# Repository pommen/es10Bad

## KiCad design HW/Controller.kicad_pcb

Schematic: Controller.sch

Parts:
1U1: 0,1U; C_0805_HandSoldering
C1: 0,1u; C_0805_HandSoldering
C2: 10u; C_0805_HandSoldering
C3: 10uF; CP_Tantalum_Case-B_EIA-3528-21_Hand
C4, C9: 0.1u; C_0805_HandSoldering
C5: 0,1U; C_0805_HandSoldering
C6, C7: 22pf; C_0805_HandSoldering
C8: 0.1; C_0805_HandSoldering
D1: WS2812B
F1: Polyfuse; LittleFuse_110F_24V
FTDI1: FTDI; Pin_Header_Angled_1x06_Pitch2.54mm
J1: Spare; Pin_Header_Straight_1x04_Pitch2.54mm
J2: +12V_con; TerminalBlock_bornier-2_P5.08mm
J3: LimitUpper; Pin_Header_Straight_1x03_Pitch2.54mm
J4: ControlSwitch; Pin_Header_Straight_1x03_Pitch2.54mm
J5: LimitLower; Pin_Header_Straight_1x03_Pitch2.54mm
J6: Motor_controller_connections; Pin_Header_Straight_1x09_Pitch2.54mm
JP1: Jumper; Pin_Header_Straight_1x03_Pitch2.54mm
R1: 10K; R_0805_HandSoldering
U1: L7805; TO-220-3_Horizontal
U2: ATMEGA328P-AU-Arduino; TQFP-32_7x7mm_Pitch0.8mm
Y1: 8MHZ; Crystal_SMD_HC49-SD_HandSoldering

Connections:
+12V: C2.1, F1.1, J3.1, J4.1, J5.1, U1.1
Dir: J6.2, U2.14
Ena: J6.6, U2.12
Fault: J6.7, U2.15
GND: 1U1.2, C2.2, C3.2, C4.2, C5.2, C6.1, C7.1, C8.2, C9.2, D1.1, FTDI1.5, FTDI1.6, J2.1, J3.2, J4.2, J5.2, J6.1, J6.3, J6.5, J6.9, JP1.1, U1.2, U2.3, U2.5, U2.21
LED: D1.2, U2.24
LimitLower: J5.3, U2.10
LimitUpper: J3.3, U2.11
unnamed: C5.1, U2.20
unnamed: C6.2, U2.7, Y1.1
unnamed: C7.2, U2.8, Y1.2
unnamed: F1.2, J2.2
RST: C1.1, FTDI1.1
RXI: FTDI1.3, U2.30
Step: J6.4, U2.13
Switch: J4.3, U2.32
TX0: FTDI1.2, U2.31
VCC: 1U1.1, C3.1, C4.1, C8.1, C9.1, D1.3, FTDI1.4, J6.8, R1.1, U1.3, U2.4, U2.6, U2.18
reset_in: C1.2, JP1.2, R1.2, U2.29
scl: U2.28
sda: U2.27

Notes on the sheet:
FTDI + ISP
Reset
Motor driver connections: Dir Step Enable Fault VCC GND
+12v IN VCC= 5v
Limit upper +,-,sig Limit lower +,-,sig toggle switch -, sig

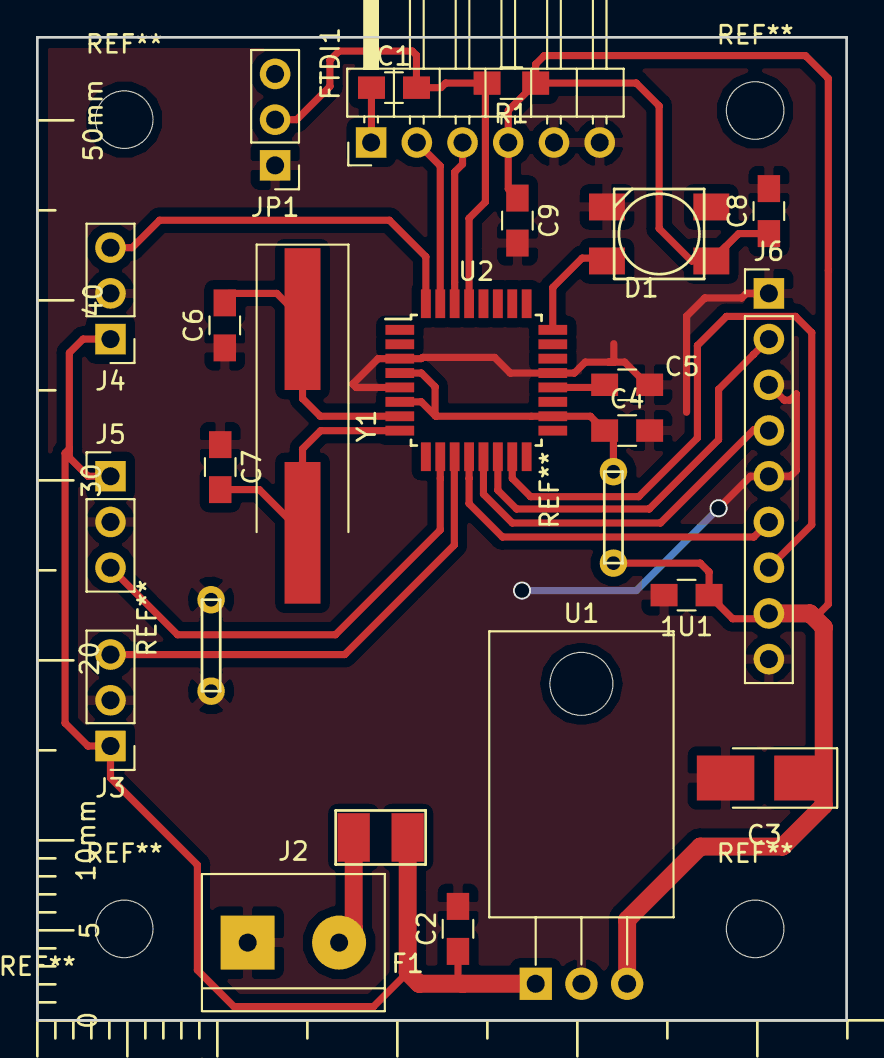
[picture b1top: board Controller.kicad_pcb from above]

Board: 2 copper layers, 45.0 x 54.6 mm, 23 parts (0 on the bottom side), 19 nets.

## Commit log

2018-04-27 Schemativ and layout
    In kicad 4.07
2018-05-03 Firmware
2018-05-03 platformio init
2018-06-04 all but done
2018-06-05 klar
2018-06-07 gcode and kicad 5
